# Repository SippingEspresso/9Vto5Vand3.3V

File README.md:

# 9Vto5Vand3.3V
9V to 5V and 3.3V for low current draw systems (&lt;5mA)

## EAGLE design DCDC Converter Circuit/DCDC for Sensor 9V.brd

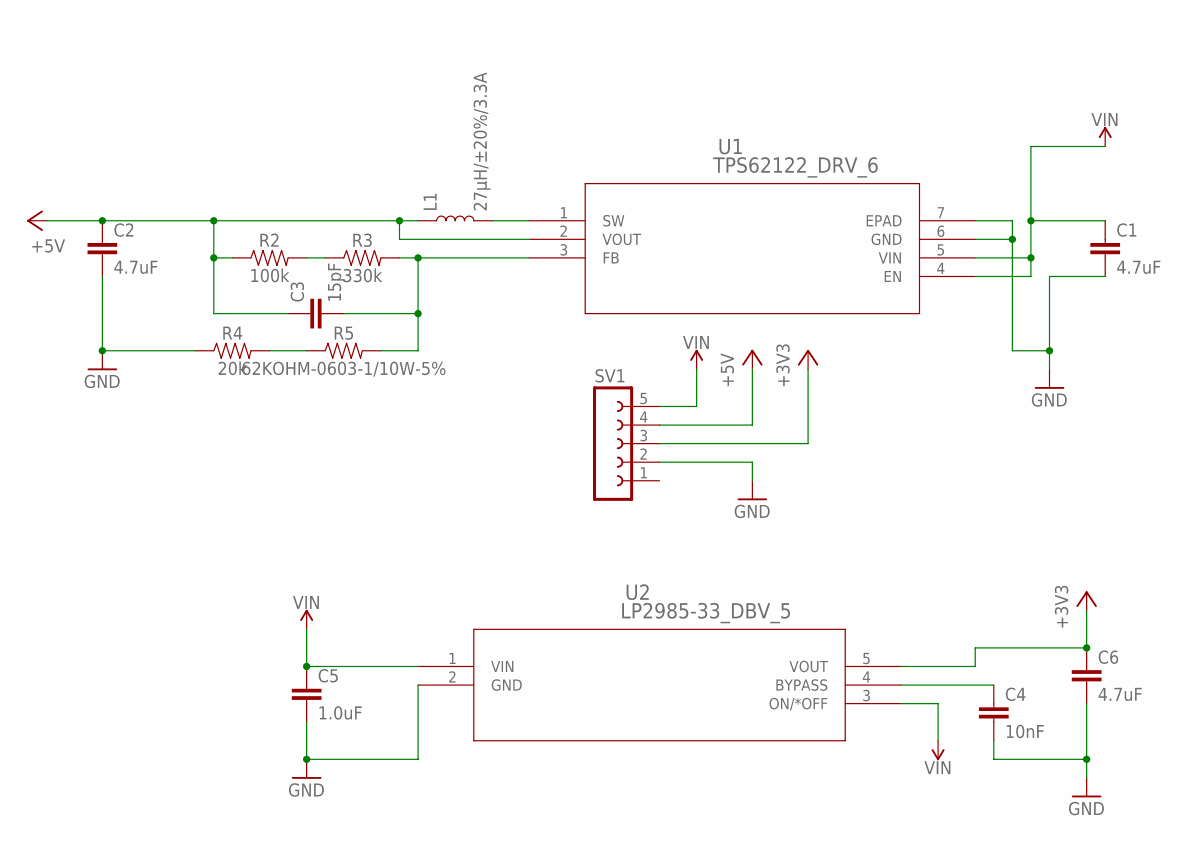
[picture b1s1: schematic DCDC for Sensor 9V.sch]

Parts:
C1, C2: 4.7uF; 1206
C3: 15pF; 0603
C4: 10nF; 0603
C5: 1.0uF; 0603
C6: 4.7uF; 0603
L1: 27µH/±20%/3.3A; INDUCTOR_SDR1307
R2: 100k; 0603
R3: 330k; 0603
R4: 20k; 0603
R5: 62KOHM-0603-1/10W-5%; 0603
SV1: FE05-1
U1: TPS62122_DRV_6; DRV6_1P6X1
U2: LP2985-33_DBV_5; DBV5

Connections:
+3V3: C6.1, SV1.3, U2.5 (VOUT)
+5V: C2.1, C3.1, L1.P$1 (1), R2.1, SV1.4, U1.2 (VOUT)
GND: C1.2, C2.2, C4.2, C5.2, C6.2, R4.1, SV1.2, U1.6 (GND), U1.7 (EPAD), U2.2 (GND)
unnamed: R4.2, R5.1
unnamed: R2.2, R3.1
unnamed: C4.1, U2.4 (BYPASS)
unnamed: L1.P$2 (2), U1.1 (SW)
unnamed: C3.2, R3.2, R5.2, U1.3 (FB)
VIN: C1.1, C5.1, SV1.5, U1.4 (EN), U1.5 (VIN), U2.1 (VIN), U2.3 (ON/*OFF)

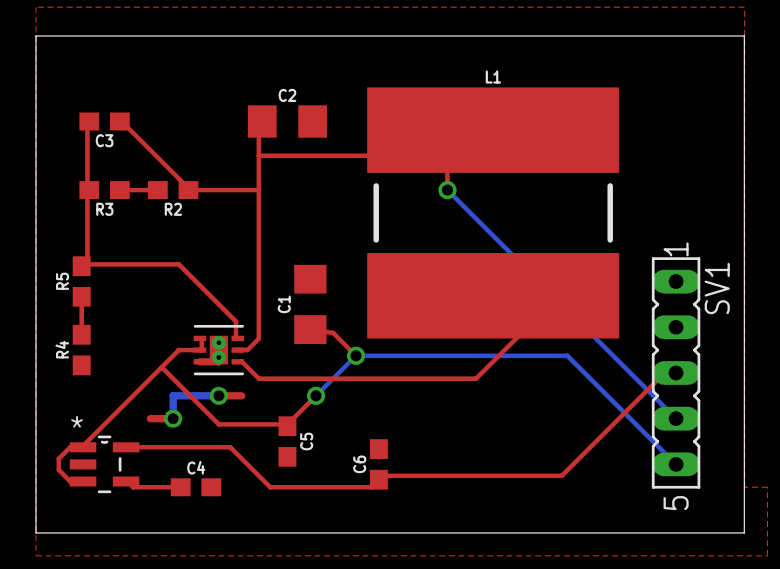
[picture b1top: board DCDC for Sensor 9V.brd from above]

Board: 2 copper layers, 39.4 x 27.6 mm, 14 parts (0 on the bottom side), 9 nets.

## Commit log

2017-02-06 DCDC Designed and done

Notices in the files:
parts and their libraries:
SparkFun-Capacitors: Licensing: Creative Commons ShareAlike 4.0 International - https://creativecommons.org/licenses/by-sa/4.0
